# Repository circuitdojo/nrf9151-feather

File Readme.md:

# Circuit Dojo - nRF9151 Feather Hardware Files

## Purchase

Considering supporting the project and purchasing a nRF9151 Feather at the following locations:

1. [The Circuit Dojo Official Store](https://www.circuitdojo.com/products/nrf9151-feather)
2. [Digikey](https://www.digikey.com/en/products/detail/circuit-dojo/PASSY-NRF9151-FEATHER/26580618)

## Code

All code for this board can be [found here.](https://github.com/circuitdojo/nRF9160-feather-examples-and-drivers/tree/v2.7.x)

## Documentation

[Documentation is available here.](https://docs.circuitdojo.com)

## License

See [**LICENSE.txt**](License.txt) for more info.

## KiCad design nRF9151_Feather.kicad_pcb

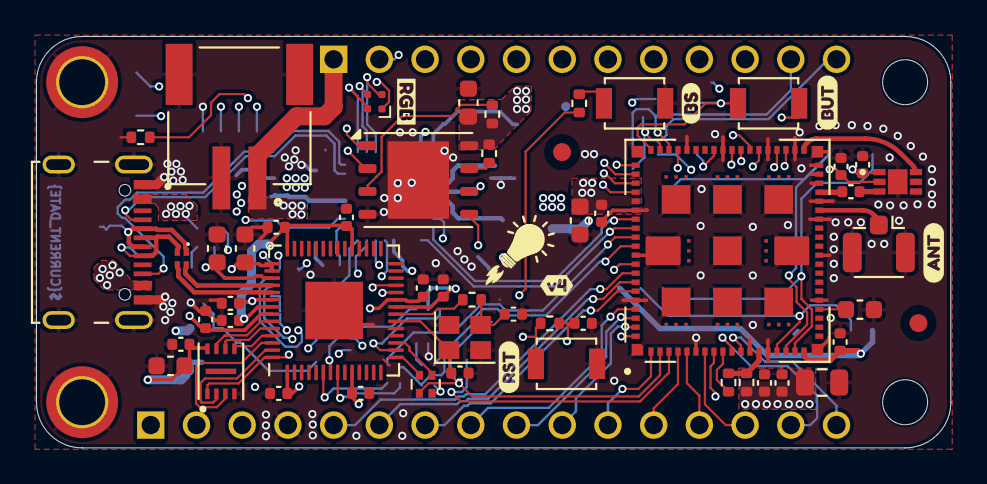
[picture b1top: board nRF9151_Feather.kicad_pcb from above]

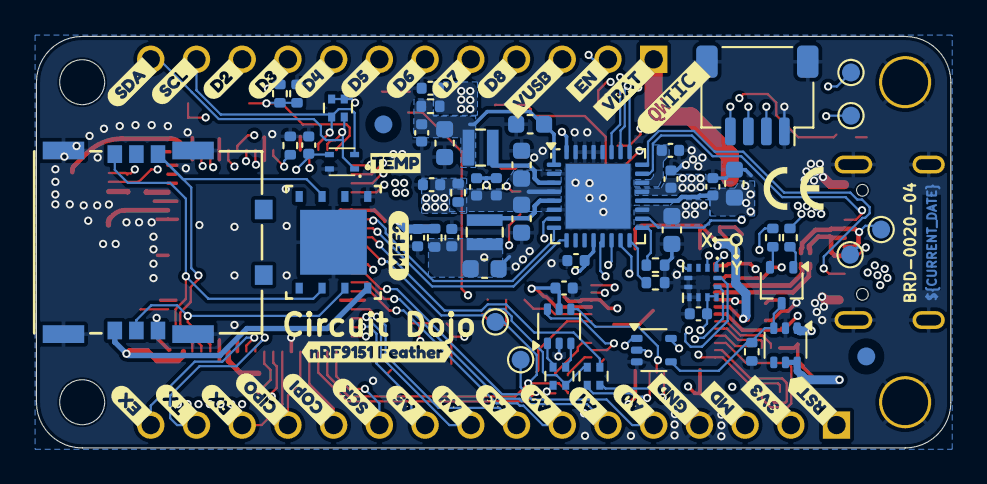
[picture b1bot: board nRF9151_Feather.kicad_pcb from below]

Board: 4 copper layers, 50.8 x 22.9 mm, 151 parts (87 on the bottom side), 103 nets.

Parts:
C1, C3: 1u; C_0402_1005Metric
C2, C5, C17, C18: 2.2u; C_0603_1608Metric
C4, C10, C11, C24, C36, C42: 10u; C_0603_1608Metric
C6, C12, C13, C14, C15, C16, C19, C20, C21, C22, C23, C25, C27, C33, C35, C37, C41, C43, C44, C45, C47, C48: 0.1u; C_0402_1005Metric
C7, C9, C26, C38: 15p; C_0402_1005Metric
C8, C32, C34: 4.7u; C_0603_1608Metric
C28: 47u; C_0805_2012Metric
C29, C30, C31, C39, C40, C46: 100p; C_0402_1005Metric
D1: 18-038BT/BDGAR6S1-CC01/10T; LED_Wurth_150044M155260
D2: BAT54CW; SOT-323_SC-70
FB1, FB2, FB3, FB4: 120; R_0402_1005Metric
H1, H2: MountingHole; MountingHole_2.5mm
H3, H4: MountingHole_Pad; MountingHole_2.5mm_Pad_TopOnly
J1: CON-HEADER-1X12-MALE-PIN
J2: CON-HEADER-1X16-MALE-PIN
J3: CON-USB-1003-030-01210-TR; CNC_TECH_1003-030-01210-TR
J4: CON-S2B-PH-SM4-TB(LF)(SN); JST_S2B-PH-SM4-TB(LF)(SN)
J5: CON-SM04B-SRSS-TB; JST_SH_SM04B-SRSS-TB_1x04-1MP_P1.00mm_Horizontal
J6: Conn_Coaxial; U.FL_Hirose_U.FL-R-SMT-1_Vertical
L1, L2: 2.2u; IND-2P0X2P0X1P2
L3: L_Ferrite_Coupled; FIL_DLM0NSM900HY2D
R1, R6, R9, R10, R13, R14: 1k; R_0402_1005Metric
R2, R4, R11, R12: 255k; R_0402_1005Metric
R3, R8: 10k; R_0402_1005Metric
R5, R7: 1M; R_0402_1005Metric
RN2, RN3, RN4: 100; R_Array_Convex_2x0402
RN5: 20k; R_Array_Convex_2x0402
SW1, SW2, SW3: SW-434153017835‎; SW_SPST_B3U-1000P
TH1: 10k; R_0402_1005Metric
TP1, TP2, TP3, TP4, TP5, TP6: TestPoint; TestPoint_Pad_D1.0mm
U1: W25Q16JVUXIQ_TR; PSON50P300X200X60-9N
U2: nPM1300-QEXX; QFN-32-1EP_5x5mm_P0.5mm_EP3.6x3.6mm
U3: 1042240820
U4: W25Q128JVPIQ; WSON-8-1EP_6x5mm_P1.27mm_EP3.4x4.3mm
U5: RP2040; QFN-56-1EP_7x7mm_P0.4mm_EP3.2x3.2mm
U6: SIM-ST-MFF2; SIM-ST-MFF2_HOL
U7: LIS2DH12TR; PQFN50P200X200100-12N
U8: TS5A3166DCKR; SOT-353_SC-70-5
U9: TC7PZ14FU; SOT-363_SC-70-6
U10: SKY65723-81; SKY65723-81_SKY-L
U11: TPS22919; SOT-363_SC-70-6
U12: nRF9151-LAXX; LGA_9151_12.1x11.1mm
U13: STS4X
U$1, U$2, U$3, U$4: FIDUCIAL-1MM; Fiducial_1mm_Mask2mm
Y1: Crystal_GND24; Crystal_SMD_2520-4Pin_2.5x2.0mm
kibuzzard-66ABB18E: G***; kibuzzard-66ABB18E
kibuzzard-66ABB181: G***; kibuzzard-66ABB181
kibuzzard-66ABCF7A: G***; kibuzzard-66ABCF7A
kibuzzard-66ABF405: G***; kibuzzard-66ABF405
kibuzzard-66AC64B8: G***; kibuzzard-66AC64B8
kibuzzard-68A8CF71: G***; kibuzzard-68A8CF71
kibuzzard-665B4C23: G***; kibuzzard-665B4C23
kibuzzard-6699D3A2: G***; kibuzzard-6699D3A2
kibuzzard-6699D3A9: G***; kibuzzard-6699D3A9
kibuzzard-6699D3B6: G***; kibuzzard-6699D3B6
kibuzzard-6699D3BF: G***; kibuzzard-6699D3BF
kibuzzard-6699D3C7: G***; kibuzzard-6699D3C7
kibuzzard-6699D3CF: G***; kibuzzard-6699D3CF
kibuzzard-6699D3D9: G***; kibuzzard-6699D3D9
kibuzzard-6699D3FF: G***; kibuzzard-6699D3FF
kibuzzard-6699D36C: G***; kibuzzard-6699D36C
kibuzzard-6699D37C: G***; kibuzzard-6699D37C
kibuzzard-6699D39A: G***; kibuzzard-6699D39A
kibuzzard-6699D40E: G***; kibuzzard-6699D40E
kibuzzard-6699D41B: G***; kibuzzard-6699D41B
kibuzzard-6699D42E: G***; kibuzzard-6699D42E
kibuzzard-6699D43F: G***; kibuzzard-6699D43F
kibuzzard-6699D44E: G***; kibuzzard-6699D44E
kibuzzard-6699D45C: G***; kibuzzard-6699D45C
kibuzzard-6699D375: G***; kibuzzard-6699D375
kibuzzard-6699D388: G***; kibuzzard-6699D388
kibuzzard-6699D393: G***; kibuzzard-6699D393
kibuzzard-6699D406: G***; kibuzzard-6699D406
kibuzzard-6699D414: G***; kibuzzard-6699D414
kibuzzard-6699D422: G***; kibuzzard-6699D422
kibuzzard-6699D429: G***; kibuzzard-6699D429
kibuzzard-6699D437: G***; kibuzzard-6699D437
kibuzzard-6699D445: G***; kibuzzard-6699D445
kibuzzard-6699D455: G***; kibuzzard-6699D455
kibuzzard-6699D464: G***; kibuzzard-6699D464
kibuzzard-66466926: G***; kibuzzard-66466926
kibuzzard-69681563: G***; kibuzzard-69681563
kibuzzard-69866146: G***; kibuzzard-69866146

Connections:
+1V1: C13.1, C14.1, C17.1, U5.23 (DVDD), U5.45 (VREG_VOUT), U5.50 (DVDD)
+3V3: C8.1, C23.1, C25.1, C30.1, C32.1, C33.1, C43.1, C48.1, FB3.2, J2.2, J5.2 (VCC), R11.1, R12.1, RN5.3 (R2.2), RN5.4 (R1.2), SW1.1, U2.12 (VDDIO), U4.8 (VCC), U7.2 (CS), U7.9 (VDD), U7.10 (VDD_IO), U8.5 (V+), U10.1 (VCC), U11.1 (VIN), U12.65 (VDD_GPIO), U13.3 (VDD)
/ACCEL_INT1: U7.12 (INT1), U12.80 (P0.19/AIN6)
/ACCEL_INT2: U7.11 (INT2), U12.72 (P0.12)
/Debugger/BOOT: R13.1, SW3.2
/Debugger/D+: J3.6 (D+), J3.8 (D+), L3.4, TP6.1
/Debugger/D-: J3.5 (D-), J3.7 (D-), L3.1, TP5.1
/Debugger/DBG_EN: D2.3, R7.1, U8.4, U11.3 (ON)
/Debugger/DBG_SWCLK: TP3.1, U5.24 (SWCLK)
/Debugger/DBG_SWDIO: TP4.1, U5.25 (SWD)
/Debugger/GPIO5: U5.7 (GPIO5), U9.4 (2Y)
/Debugger/GPIO13: U5.16 (GPIO13), U9.6 (1Y)
/Debugger/RP2040_VDDIO: C5.1, C6.1, C12.1, C15.1, C16.1, C19.1, C20.1, C21.1, C47.1, U1.8 (VCC), U5.1 (IOVDD), U5.10 (IOVDD), U5.22 (IOVDD), U5.33 (IOVDD), U5.42 (IOVDD), U5.49 (IOVDD), U9.5 (V_{CC}), U11.5 (QOD), U11.6 (VOUT)
/Debugger/RP_D+: L3.3, U5.47 (USB_DP)
/Debugger/RP_D-: L3.2, U5.46 (USB_DM)
/Debugger/RX: RN3.4 (R1.2), RN4.2 (R2.1), U12.70 (P0.11)
/Debugger/SWDCLK: RN2.3 (R2.2), TP2.1, U12.3 (SWDCLK)
/Debugger/SWDIO: TP1.1, U8.2, U12.4 (SWDIO)
/Debugger/TX: RN3.3 (R2.2), U12.69 (P0.10)
/Debugger/VDDIO_EN: R9.1, U2.7 (GPIO0)
/EN: J1.2, U2.15 (SHPHLD)
/Headers/A0: J2.5, U12.73 (P0.13/AIN0)
/Headers/A1: J2.6, U12.74 (P0.14/AIN1)
/Headers/A2: J2.7, U12.75 (P0.15/AIN2)
/Headers/A3: J2.8, U12.77 (P0.16/AIN3)
/Headers/A4: J2.9, U12.78 (P0.17/AIN4)
/Headers/A5: J2.10, U12.79 (P0.18/AIN5)
/Headers/CIPO: J2.13, U12.6 (P0.22/TRACEDATA0)
/Headers/COPI: J2.12, U12.5 (P0.21/TRACECLK)
/Headers/D2: J1.10, U12.44 (P0.26)
/Headers/D3: J1.9, U12.45 (P0.27)
/Headers/D4: J1.8, U12.47 (P0.28)
/Headers/D5: J1.7, U12.48 (P0.29)
/Headers/D6: J1.6, U12.49 (P0.30)
/Headers/D7: J1.5, U12.50 (P0.31)
/Headers/D8: J1.4, U12.56 (P0.00)
/Headers/EXTRA: J2.16, U12.12 (P0.25/TRACEDATA3)
/Headers/MODE/WAKE: J2.3, R10.1
/Headers/RX: J2.14, U12.8 (P0.23/TRACEDATA1)
/Headers/SCK: J2.11, U12.2 (P0.20/AIN7)
/Headers/TX: J2.15, U12.11 (P0.24/TRACEDATA2)
/Headers/~RESET: J2.1, R1.1, SW2.1
/I2C_SCL: J1.11, J5.4 (SCL), RN5.1 (R1.1), U2.14 (SCL), U7.1 (SCL/SPC), U12.57 (P0.01), U13.2 (SCL)
/I2C_SDA: J1.12, J5.3 (SDA), RN5.2 (R2.1), U2.13 (SDA), U7.4 (SDA/SDI/SDO), U12.58 (P0.02), U13.1 (SDA)
/PMIC_INT1: U2.8 (GPIO1), U12.67 (P0.08)
/PMIC_INT2: U2.9 (GPIO2), U12.68 (P0.09)
/Power/CC1: J3.4 (CC1), U2.23 (CC1)
/Power/CC2: J3.10 (CC2), U2.24 (CC2)
/Power/PMIC_SW1: L1.1, U2.3 (SW1)
/Power/PMIC_SW2: L2.1, U2.5 (SW2)
/Processor/BUTTON: R8.1, R10.2, SW1.2, U12.59 (P0.03)
/Processor/COEX0: C41.1, R5.1, U10.2 (VEN), U12.52 (COEX0)
/Processor/FLASH_CS: U4.1 (~CS), U12.61 (P0.04)
/Processor/FLASH_MISO: U4.2 (DO(IO1)), U12.62 (P0.05)
/Processor/FLASH_MOSI: U4.5 (DI(IO0)), U12.64 (P0.07)
/Processor/FLASH_SCK: U4.6 (CLK), U12.63 (P0.06)
/Processor/RF_ANT: J6.1 (In), U12.35 (ANT)
/Processor/RF_AUX: C38.2, U12.37 (AUX)
/Processor/RF_GPS: U10.6 (RF_OUT), U12.42 (GPS)
/Processor/RF_IN: C38.1, U10.3 (RF_IN)
/Processor/SIM_CLK: U3.S3 (CLK), U6.6 (CLK), U12.18 (SIM_CLK)
/Processor/SIM_IO: U3.S6 (I/O), U6.3 (I/O), U12.17 (SIM_IO)
/Processor/SIM_RST: U3.S2 (RST), U6.7 (RST), U12.16 (SIM_RST)
/Processor/SIM_VCC: C37.1, U3.S1 (VCC), U6.8 (VCC), U12.19 (SIM_1V8)
GND: C1.2, C2.2, C3.2, C4.2, C5.2, C6.2, C7.2, C8.2, C9.2, C10.2, C11.2, C12.2, C13.2, C14.2, C15.2, C16.2, C17.2, C18.2, C19.2, C20.2, C21.2, C22.2, C23.2, C24.2, C25.2, C26.2, C27.2, C28.2, C29.2, C30.2, C31.2, C32.2, C33.2, C34.2, C35.2, C36.2, C37.2, C39.2, C40.2, C41.2, C42.2, C43.2, C44.2, C45.2, C46.2, C47.2, C48.2, H3.1, H4.1, J2.4, J3.1 (GND), J3.12 (GND), J3.S3 (SHIELD), J3.S4 (SHIELD), J3.S5 (SHIELD), J3.S6 (SHIELD), J4.2, J4.S1 (SHIELD), J4.S2 (SHIELD), J5.1 (GND), J5.MP (SH), J6.2 (Ext), R2.2, R4.2, R5.2, R7.2, R8.2, SW2.2, SW3.1, TH1.2, U1.4 (GND), U2.2 (PVSS1), U2.6 (PVSS2), U2.28 (LSIN1/VINLDO1), U2.29 (LSOUT1/VOUTLDO1), U2.30 (LSIN2/VINLDO2), U2.31 (LSOUT2/VOUTLDO2), U2.33 (AVSS), U3.G1 (GND), U3.G2 (GND), U3.G3 (GND), U3.G4 (GND), U3.S4 (GND), U4.4 (GND), U4.9 (EP), U5.19 (TESTEN), U5.57 (GND), U6.1 (GND), U6.9 (EPAD), U7.5 (RES), U7.6 (GND), U7.7 (GND__1), U7.8 (GND__2), U8.3 (GND), U9.2 (GND), U10.7 (GND), U11.2 (GND), U12.1 (GND), U12.7 (GND), U12.13 (GND), U12.15 (GND), U12.20 (GND), U12.25 (GND), U12.30 (GND), U12.34 (GND), U12.36 (GND), U12.38 (GND), U12.39 (GND), U12.40 (GND), U12.41 (GND), U12.43 (GND), U12.46 (GND), U12.51 (GND), U12.55 (GND), U12.60 (GND), U12.66 (GND), U12.71 (GND), U12.76 (GND), U12.105 (GND), U12.106 (GND), U12.107 (GND), U12.108 (GND), U12.109 (GND), U12.110 (GND), U12.111 (GND), U12.112 (GND), U12.113 (GND), U13.4 (VSS), Y1.2, Y1.4
unnamed: C9.1, R14.2, Y1.3
unnamed: D1.4 (BK), U2.27 (LED2)
unnamed: D1.3 (GK), U2.26 (LED1)
unnamed: D1.2 (RK), U2.25 (LED0)
unnamed: D2.1, R6.2
unnamed: D2.2, R9.2
unnamed: RN2.1 (R1.1), U5.17 (GPIO14)
unnamed: RN2.4 (R1.2), RN4.1 (R1.1), U8.1
unnamed: RN2.2 (R2.1), U5.15 (GPIO12)
unnamed: RN3.1 (R1.1), U5.8 (GPIO6)
unnamed: RN3.2 (R2.1), U5.6 (GPIO4)
unnamed: RN4.4 (R1.2), U9.1 (1A)
unnamed: RN4.3 (R2.2), U9.3 (2A)
unnamed: U1.6 (CLK), U5.52 (QSPI_SCLK)
unnamed: U1.5 (IO0), U5.53 (QSPI_SD0)
unnamed: U1.2 (IO1), U5.55 (QSPI_SD1)
unnamed: U1.3 (IO2), U5.54 (QSPI_SD2)
unnamed: U1.7 (IO3), U5.51 (QSPI_SD3)
unnamed: R13.2, U1.1 (~CS), U5.56 (QSPI_SS)
unnamed: TH1.1, U2.18 (NTC)
unnamed: C4.1, C36.1, C40.1, C44.1, FB4.1, U2.4 (PVDD)
unnamed: C3.1, U2.22 (VBUSOUT)
unnamed: C11.1, C29.1, C42.1, FB3.1, L1.2, U2.1 (VOUT1)
unnamed: C24.1, C31.1, FB2.1, L2.2, U2.32 (VOUT2)
unnamed: R2.1, U2.17 (VSET1)
unnamed: R4.1, U2.16 (VSET2)
unnamed: R12.2, U4.3 (IO2(~WP))
unnamed: R11.2, U4.7 (IO3(~HOLD))
unnamed: C7.1, U5.20 (XIN), Y1.1
unnamed: R14.1, U5.21 (XOUT)
unnamed: C34.1, U12.24 (DEC0)
unnamed: R3.2, U12.10 (ENABLE)
unnamed: FB1.2, R3.1, U12.14 (VDD)
unnamed: C35.1, R1.2, U12.9 (~RESET)
VBAT: C2.1, J1.1, J4.1, U2.19 (VBAT)
VBUS: C1.1, J1.3, J3.2 (VBUS), J3.11 (VBUS), R6.1, U2.21 (VBUS)
VCC: C18.1, C22.1, C39.1, FB2.2, U5.43 (ADC_AVDD), U5.44 (VREG_IN), U5.48 (USB_VDD)
VSYS: C10.1, C26.1, C27.1, C28.1, C45.1, C46.1, D1.1 (A), FB1.1, FB4.2, U2.20 (VSYS)

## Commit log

2025-05-06 Release v1
2025-05-22 Fixing error in schematic w/ nRST
    nRST on debugger should not (and is not) connected to the nRST signal to the processor. Cleaning up schematic to clear up confusion around that. PCB routing remains unchanged.
2025-07-21 Updating parts:
    1. Button change
    2. USB change
2025-07-21 Removing letter since it's in doc
2025-09-02 v2 Changes:
    1. Added STS4x to sensors
    2. Relocated NTC away from nPM1300
    3. Updated footprint for new USB connector
    4. Optimized other footprint paste aperture
2025-10-08 Fixing pinout for new USB connector
2025-10-15 Adding variant control
2026-05-25 PCB cleanup: reduce ground connections and set isolation to 0.2mm
    - Reducing the size of ground connections
    - Changing isolation to 0.2mm for all layers
    - Adding border isolation 0.2mm

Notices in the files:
parts and their libraries:
Copyright 2016 Accelerated Designs. All rights reserved.
